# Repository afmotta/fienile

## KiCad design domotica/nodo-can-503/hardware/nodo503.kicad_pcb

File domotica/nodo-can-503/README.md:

# Nodo CAN 503 – ESP32-C6-WROOM-1 (rev C)

Nodo per la domotica CAN del fienile, da montare in scatola 503: un morsetto per 24 V e bus CAN, transceiver TJA1051T/3, 6 ingressi pulsante, porta Qwiic (I²C) e modulo **ESP32-C6-WROOM-1-N8** (LCSC C5366877) con Wi-Fi per ESPHome e aggiornamenti OTA. È pensato per il montaggio completo da JLCPCB, con tutti i componenti su un solo lato.

- **Dimensioni:** 56 × 41 mm (come la CANBed RP2040), 2 strati, spessore 1,6 mm, rame 1 oz
- **Fissaggio:** 4 fori M3 non metallizzati (Ø 3,2 mm) negli angoli, con il centro a 3,5 mm dai bordi: interasse **49 × 34 mm**. Entro 3,3 mm dal centro di ogni foro non passano piste né via, così la testa della vite (fino a Ø 6 mm) appoggia solo su piano di massa coperto da solder mask. Il foro in alto a sinistra è a circa 4 mm dall'antenna: lì usa una vite in nylon o un perno di plastica.
- **Progetto:** KiCad 7 (si apre anche in KiCad 8/9)
- **Simbolo e footprint del modulo:** dalla libreria ufficiale [espressif/kicad-libraries](https://github.com/espressif/kicad-libraries), licenza CC-BY-SA 4.0. Il footprint comprende anche l'area dell'antenna senza rame.

## Contenuto della cartella

Questa cartella (`domotica/nodo-can-503/` nel repository `afmotta/fienile`) contiene tutto il progetto della scheda; i percorsi sono relativi a qui.

| Percorso | Cosa contiene |
|---|---|
| `hardware/nodo503.kicad_pro / .kicad_sch / .kicad_pcb` | Progetto KiCad 7 completo (si apre con KiCad 7, 8 o 9) |
| `hardware/nodo503.kicad_sym`, `hardware/nodo503.pretty/` | Simbolo e footprint del modulo ESP32-C6-WROOM-1 (libreria di progetto) |
| `hardware/out/gerber_JLCPCB.zip` | Gerber + foratura, da caricare così com'è su JLCPCB |
| `hardware/out/BOM.csv`, `CPL_JLCPCB.csv` | Distinta e piazzamento per il montaggio completo (SMD + THT) |
| `hardware/out/BOM_SMD.csv`, `CPL_SMD.csv` | Distinta e piazzamento solo SMD |
| `hardware/out/nodo503_schema.pdf`, `anteprima_lato_*.png` | Schema elettrico e anteprime rame + serigrafia |
| `hardware/jlc_library.json` | Libreria JLCPCB (Basic / Preferred / Extended) di ogni codice LCSC |
| `hardware/*.py`, `hardware/*.sh` | Script che generano schema, PCB, sbroglio e file di produzione (vedi [docs/pipeline.md](docs/pipeline.md)) |
| `docs/decisioni.md` | Storia del progetto e motivazioni delle scelte |
| `docs/pipeline.md` | Come rigenerare tutto, struttura degli script, problemi noti |
| `CLAUDE.md` | Contesto per le sessioni di Claude Code che lavoreranno sul progetto |
| `tools/setup.sh` | Installa KiCad 7, Freerouting 1.9.0 e le dipendenze Python |

Per rigenerare i file di produzione dopo una modifica: `sudo tools/setup.sh` (una volta), poi `hardware/route.sh` se cambiano piazzamento o collegamenti, `hardware/build_pcb.sh` se basta lo sbroglio salvato, e infine `hardware/export.sh`.

## Circuito

- **Ingresso 24 V:** PTC da 0,5 A (F1), diodo SS34 contro l'inversione di polarità (D1), TVS SMBJ26CA (D2), elettrolitico da 22 µF e MLCC da 10 µF 50 V in ingresso.
- **5 V:** MORNSUN K7805-500R3 (U1), switching con pin compatibili 7805. Alimenta il TJA1051.
- **3,3 V:** LDO AP2112K-3.3 (U4, 600 mA). Due diodi B5819W (D3, D5) in "OR" lo alimentano dai 5 V del K7805 oppure dai 5 V del pettine di programmazione: il modulo si programma anche senza i 24 V, e la tensione dell'USB non risale verso il K7805.
- **CAN:** TJA1051T/3 con VIO a 3,3 V (nessun partitore sulle linee logiche), pin S a GND, protezione ESD NUP2105L sulle linee del bus. **Nessuna terminazione da 120 Ω** a bordo: il bus va terminato agli estremi della linea.
- **Microcontrollore:** modulo ESP32-C6-WROOM-1-N8 (flash 8 MB, antenna su PCB), con l'antenna a filo del bordo superiore della scheda. Rete RC su EN (10 kΩ + 1 µF) e pull-up da 10 kΩ su GPIO8, come raccomanda Espressif.
- **Ingressi pulsante:** per ciascuno pull-up da 10 kΩ a 3,3 V, resistenza in serie da 1 kΩ e condensatore da 100 nF verso GND (τ ≈ 100 µs). Il pulsante chiude verso GND (logica attiva bassa). Componenti 0402, sotto il bordo inferiore del modulo.

## Pinout

| Funzione | GPIO | Pin modulo WROOM |
|---|---|---|
| CAN TXD | GPIO23 | 21 |
| CAN RXD | GPIO22 | 20 |
| Pulsante 1 | GPIO7 | 7 |
| Pulsante 2 | GPIO0 | 8 |
| Pulsante 3 | GPIO1 | 9 |
| Pulsante 4 | GPIO20 | 18 |
| Pulsante 5 | GPIO19 | 17 |
| Pulsante 6 | GPIO18 | 16 |
| Qwiic SDA | GPIO3 | 26 |
| Qwiic SCL | GPIO2 | 27 |
| USB D− / D+ (programmazione) | GPIO12 / GPIO13 | 13 / 14 |
| BOOT (pin 5 di J4) | GPIO9 | 15 |
| Pull-up di boot | GPIO8 | 10 |
| Liberi | GPIO4, 5, 6, 10, 11, 15, 16, 17, 21 | – |

Rispetto alla versione 48 × 44 mm i GPIO di pulsanti, Qwiic e CAN sono cambiati: i pulsanti 1–3 usano i pin del lato sinistro del modulo, i pulsanti 4–6 quelli del lato destro, così le piste non si incrociano. GPIO4, GPIO5, GPIO8, GPIO9 e GPIO15 sono pin di strapping: se in futuro ne usi uno, tieni conto del livello che deve avere all'avvio.

## Connettori

- **J1 BUS:** morsetto passo 3,5 mm sul bordo destro, fili che entrano da destra. Dall'alto in basso: 24V – GND – CAN-H – CAN-L.
- **J2 PULSANTI:** morsetto estraibile verticale a 7 poli, passo 3,5 mm, sul bordo inferiore. Sulla scheda c'è la presa (Kefa KF2EDGV-3.5-7P); i fili vanno nella spina a vite (KF2EDGK-3.5-7P), che si innesta dall'alto, quindi i fili escono perpendicolari alla scheda. Cabli la spina sui pulsanti e poi la innesti: per staccare la scheda basta sfilarla. Pin da sinistra: pulsanti 1, 2, 3, 4, 5, 6, GND.
- **Comune dei pulsanti:** c'è un solo morsetto GND. Fai i ponticelli del comune tra i pulsanti sulla placca e porta un solo filo alla spina. Se preferisci due fili fino alla spina, il morsetto da 1,5 mm² ne accetta due da 0,5 mm², meglio con un puntale doppio.
- **Filo per i pulsanti:** la corrente è di circa 0,3 mA, quindi la sezione conta solo per la meccanica. Consigliata cordina da **0,5 mm²** (la spina accetta da 0,2 a 1,5 mm²). Se nella scatola o nei tubi passano anche conduttori a 230 V, il filo deve avere un isolamento adatto a quella tensione (ad esempio FS17 o H05V-K da 0,5 mm²).
- **J3 Qwiic:** JST SH a 4 pin, passo 1 mm, sul bordo superiore a destra con l'imbocco verso l'alto. GND, 3,3 V, SDA, SCL. **Nessun pull-up I²C sulla scheda:** li forniscono il QwiicBus e le schede dei sensori.
- **J4 PROG:** pettine verticale 1×6 a passo 2,54 mm sul lato sinistro, da non montare. Pin: 5V, D−, D+, GND, BOOT, GND. I pin 1–4 vanno al cavo USB (USB nativo del C6). Un ponticello sui pin 5–6 porta GPIO9 a massa e fa partire il modulo in modalità download.

Nessuna terminazione da 120 Ω sulla scheda: il bus va terminato agli estremi della linea.

## Prima programmazione

1. Collega un cavo USB al pettine J4: rosso al 5V, bianco a D−, verde a D+, nero a GND. Puoi usare un connettore a pettine o delle punte a molla (pogo pin).
2. Con il flash vuoto il modulo di solito entra da solo in modalità download. Se non succede, o se un firmware difettoso ha bloccato l'USB:
   - metti un ponticello sui pin 5–6 di J4 (BOOT–GND);
   - collega l'USB, oppure accendi la scheda;
   - programma, poi **togli il ponticello**. Se lo lasci, il modulo resta in modalità download a ogni riavvio e il firmware non parte.
3. Programma con ESPHome (o esptool) via USB. Dal flash successivo puoi usare l'OTA via Wi-Fi.

## Da verificare prima dell'ordine

1. **Codici LCSC e magazzino.** Tutti i componenti montati hanno un codice LCSC. Al caricamento della BOM controlla la disponibilità, soprattutto di J3 (vedi sotto).
2. **Rotazioni nel file CPL.** Controllale nell'anteprima di assemblaggio JLCPCB, soprattutto per il modulo U3 (l'antenna deve stare a filo del bordo superiore, sopra l'area senza rame), U2, U4 (ruotato di 180°), J3 (ruotato di 180°, imbocco verso l'alto), J1 (ruotato di 90°), J2 (il lato con l'incastro della spina deve coincidere con quello del footprint), i diodi e C1.
3. **Via nel pad di massa del modulo.** Il pad di massa sotto il WROOM è una griglia 3×3 con 5 via verso la massa sul retro. Su JLCPCB conviene chiedere che le via siano tappate ("via-in-pad" o "epoxy filled"), così lo stagno non cola nei fori. Se non lo fai, di solito funziona comunque.
4. **Piste sotto il modulo.** La pista di BOOT passa sullo strato superiore sotto il bordo inferiore del modulo, lontano dall'antenna; altre piste passano sul retro sotto il modulo. È ammesso, ma se in KiCad vuoi un piano di massa più pulito sotto il modulo puoi spostarle sul retro.

## Montaggio

- **Montaggio completo:** carica `BOM.csv` e `CPL_JLCPCB.csv`. JLCPCB monta anche i THT (K7805-500R3, J1 e la presa J2) a onda o a mano. Non resta nulla da saldare, J4 resta senza componente. La spina KF2EDGK-3.5-7P si ordina a parte.
- **Solo SMD:** carica `BOM_SMD.csv` e `CPL_SMD.csv`. Il K7805, J1 e la presa J2 restano da saldare a mano.

## Esempio ESPHome (indicativo)

```yaml
esp32:
  board: esp32-c6-devkitc-1
  variant: esp32c6
  framework:
    type: esp-idf

canbus:
  - platform: esp32_can
    tx_pin: GPIO23
    rx_pin: GPIO22
    can_id: 0x101
    bit_rate: 125kbps

i2c:
  sda: GPIO3
  scl: GPIO2
  scan: true

binary_sensor:
  - platform: gpio
    name: "Pulsante 1"
    pin:
      number: GPIO7
      inverted: true
      mode: { input: true, pullup: false }   # pull-up esterno da 10k
    filters:
      - delayed_on_off: 20ms
  # Pulsanti 2–6: GPIO0, GPIO1, GPIO20, GPIO19, GPIO18
```

## BOM e librerie JLCPCB (aggiornata il 2026-10-14)

Tutti i componenti hanno un codice LCSC e sono pensati per il montaggio completo da JLCPCB, compresi i THT (J1, J2 e K7805 U1, saldati da JLCPCB a onda o a mano). La colonna **Libreria JLCPCB** della BOM indica Basic / Preferred / Extended; l'elenco usato è in `hardware/jlc_library.json`.

- **Non montati:** solo **J4** (pettine di programmazione, DNP). Per programmare si usano pin a pressione o un pettine inserito al momento.
- **C2** è passato da 2,2 µF a **10 µF 50 V 1206** (C13585, Basic): più capacità in ingresso al K7805 e un componente Extended in meno.
- **C1:** Panasonic EEE-FK1H220P (C128458), 6,3 × 5,8 mm. È compatibile con il footprint 6,3 × 5,4 mm.
- **J1:** DORABO DB125-3.5-4P-GN-S (C2757925, Extended, saldatura a onda, disponibile anche in PCBA Economic), passo 3,5 mm, ingresso fili laterale, vite M2, filo fino a 1 mm². Il passo coincide con il footprint Phoenix PT 1,5/4-3,5-H. Prima dell'ordine verifica nell'anteprima JLCPCB che il corpo e il lato d'ingresso dei fili coincidano.
- **J2:** presa Kefa KF2EDGV-3.5-7P (C441326, Extended, saldatura a onda, PCBA Economic e Standard), footprint Phoenix MCV 1,5/7-G-3,5 verticale. A magazzino LCSC ce n'erano 485 il 2026-10-14.
- **Spina per J2 da ordinare a parte:** Kefa KF2EDGK-3.5-7P (LCSC C440852, circa 0,52 $ da 10 pezzi). Non è nella BOM di montaggio perché non si salda: si aggiunge all'ordine LCSC. Il 2026-10-14 ce n'erano solo 234: comprale con il primo ordine, con qualcuna di scorta. Se finissero, la soluzione di riserva sono due 4 poli (KF2EDGV/KF2EDGK-3.5-4P, C441323/C440849, molto disponibili), ma servirebbe rifare il PCB. 
- **CPL:** per i THT la posizione è il centro dei pin (non il pin 1). Controlla nell'anteprima di assemblaggio le rotazioni dei morsetti e del K7805.
- **J3 (C160404) ha pochissimi pezzi a magazzino.** Alternative compatibili Qwiic (Extended, da confrontare con il footprint): ZX-SH1.0-4PWT C7430446, HC-1.0-4PWT C2845363, BX-SH1.0-4PWT C18077910.
- Le pagine JLCPCB dei componenti Preferred mostrano solo "Extended": al caricamento della BOM verifica che abbiano il badge "Preferred".

## Storia e decisioni

La storia del progetto (rev A con XIAO, rev B con MINI-1, revisione di un esperto, passaggio a 56 × 41 mm, scelta dei connettori) e il motivo di ogni scelta sono in [docs/decisioni.md](docs/decisioni.md).

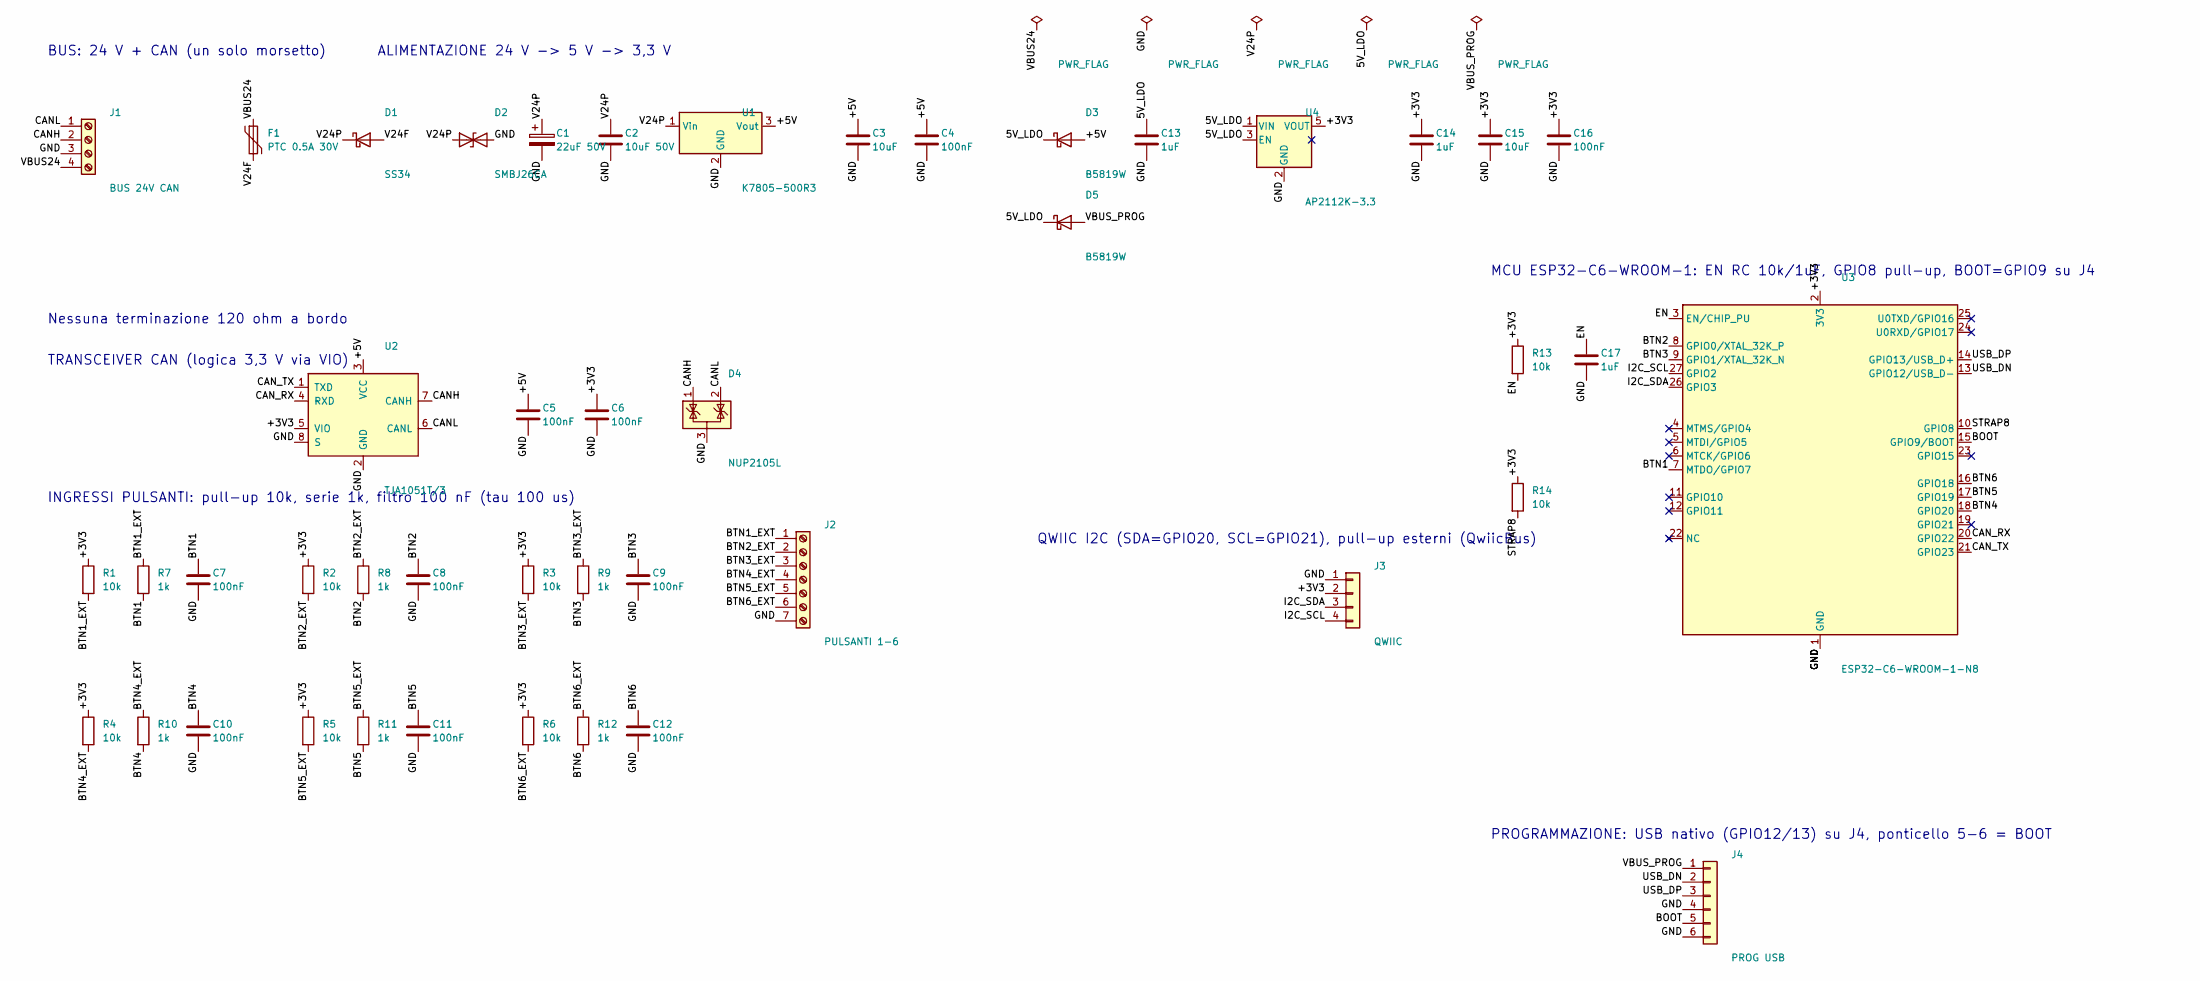
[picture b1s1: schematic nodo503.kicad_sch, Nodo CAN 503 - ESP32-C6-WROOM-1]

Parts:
C1: 22uF 50V; CP_Elec_6.3x5.4; MPN Panasonic EEE-FK1H220P, elettrolitico S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; LCSC C128458
C2: 10uF 50V; C_1206_3216Metric; MPN MLCC 10 uF 50 V X5R 1206 (Samsung CL31A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; LCSC C13585
C3: 10uF; C_0805_2012Metric; MPN MLCC 10 uF 25 V 0805; LCSC C15850
C4, C5, C6, C16: 100nF; C_0603_1608Metric; MPN MLCC 100 nF 50 V 0603; LCSC C14663
C7, C8, C9, C10, C11, C12: 100nF; C_0402_1005Metric; MPN MLCC 100 nF 0402; LCSC C1525
C13, C14: 1uF; C_0603_1608Metric; MPN MLCC 1 uF 50 V X5R 0603 (Samsung CL10A1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; LCSC C15849
C15: 10uF; C_0603_1608Metric; MPN MLCC 10 uF 10 V X5R 0603 (Samsung CL10A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; LCSC C19702
C17: 1uF; C_0402_1005Metric; MPN MLCC 1 uF 25 V X5R 0402 (Samsung CL05A1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; LCSC C52923
D1: SS34; D_SMA; MPN SS34 (40 V 3 A) - protezione inversione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; LCSC C8678
D2: SMBJ26CA; D_SMB; MPN SMBJ26CA TVS bidirezionale 26 V, SMB (h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; LCSC C19077581
D3: B5819W; D_SOD-123; MPN B5819W - OR alimentazione LDO (da 5 V b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; LCSC C8598
D4: NUP2105L; SOT-23; MPN onsemi NUP2105LT1G - ESD bus CAN 24 V; LCSC C14486
D5: B5819W; D_SOD-123; MPN B5819W - OR alimentazione LDO (da USB d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; LCSC C8598
F1: PTC 0.5A 30V; Fuse_1812_4532Metric; MPN PTC 1812 RUILON SMD1812P050TF/30 (0,5 A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; LCSC C12559
J1: BUS 24V CAN; TerminalBlock_Phoenix_PT-1,5-4-3.5-H_1x04_P3.50mm_Horizontal; MPN Morsetto a vite 4 poli passo 3,5 mm, DO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; LCSC C2757925
J2: PULSANTI 1-6; PhoenixContact_MCV_1,5_7-G-3.5_1x07_P3.50mm_Vertical; MPN Presa per morsetto estraibile verticale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; LCSC C441326
J3: QWIIC; JST_SH_SM04B-SRSS-TB_1x04-1MP_P1.00mm_Horizontal; MPN JST SM04B-SRSS-TB(LF)(SN) (Qwiic, SH 1 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; LCSC C160404
J4: PROG USB; PinHeader_1x06_P2.54mm_Vertical; MPN Pettine 1x6 2,54 mm (non montato): 5V, 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
R1, R2, R3, R4, R5, R6, R13: 10k; R_0402_1005Metric; MPN 10 kOhm 1% 0402; LCSC C25744
R7, R8, R9, R10, R11, R12: 1k; R_0402_1005Metric; MPN 1 kOhm 1% 0402; LCSC C11702
R14: 10k; R_0402_1005Metric; MPN 10 kOhm 1% 0402 (GPIO8 alto al boot); LCSC C25744
U1: K7805-500R3; Converter_DCDC_TRACO_TSR-1_THT; MPN MORNSUN K7805-500R3 (6,5-36 V -> 5 V 0,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; LCSC C86735
U2: TJA1051T/3; SOIC-8_3.9x4.9mm_P1.27mm; MPN NXP TJA1051T/3/1J; LCSC C38695
U3: ESP32-C6-WROOM-1-N8; ESP32-C6-WROOM-1; MPN Espressif ESP32-C6-WROOM-1-N8; LCSC C5366877
U4: AP2112K-3.3; SOT-23-5; MPN Diodes AP2112K-3.3TRG1 (LDO 600 mA); LCSC C51118

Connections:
5V_LDO: C13.1, D3.1 (K), D5.1 (K), U4.1 (VIN), U4.3 (EN)
+3V3: C6.1, C14.1, C15.1, C16.1, J3.2, R1.1, R2.1, R3.1, R4.1, R5.1, R6.1, R13.1, R14.1, U2.5 (VIO), U3.2 (3V3), U4.5 (VOUT)
+5V: C3.1, C4.1, C5.1, D3.2 (A), U1.3 (Vout), U2.3 (VCC)
BOOT: J4.5, U3.15 (GPIO9/BOOT)
BTN1: C7.1, R7.2, U3.7 (MTDO/GPIO7)
BTN1_EXT: J2.1, R1.2, R7.1
BTN2: C8.1, R8.2, U3.8 (GPIO0/XTAL_32K_P)
BTN2_EXT: J2.2, R2.2, R8.1
BTN3: C9.1, R9.2, U3.9 (GPIO1/XTAL_32K_N)
BTN3_EXT: J2.3, R3.2, R9.1
BTN4: C10.1, R10.2, U3.18 (GPIO20)
BTN4_EXT: J2.4, R4.2, R10.1
BTN5: C11.1, R11.2, U3.17 (GPIO19)
BTN5_EXT: J2.5, R5.2, R11.1
BTN6: C12.1, R12.2, U3.16 (GPIO18)
BTN6_EXT: J2.6, R6.2, R12.1
CANH: D4.1 (K), J1.2, U2.7 (CANH)
CANL: D4.2 (K), J1.1, U2.6 (CANL)
CAN_RX: U2.4 (RXD), U3.20 (GPIO22)
CAN_TX: U2.1 (TXD), U3.21 (GPIO23)
EN: C17.1, R13.2, U3.3 (EN/CHIP_PU)
GND: C1.2, C2.2, C3.2, C4.2, C5.2, C6.2, C7.2, C8.2, C9.2, C10.2, C11.2, C12.2, C13.2, C14.2, C15.2, C16.2, C17.2, D2.2 (A2), D4.3 (A), J1.3, J2.7, J3.1, J4.4, J4.6, U1.2 (GND), U2.2 (GND), U2.8 (S), U3.1 (GND), U3.28 (GND), U3.29 (GND), U4.2 (GND)
I2C_SCL: J3.4, U3.27 (GPIO2)
I2C_SDA: J3.3, U3.26 (GPIO3)
STRAP8: R14.2, U3.10 (GPIO8)
USB_DN: J4.2, U3.13 (GPIO12/USB_D-)
USB_DP: J4.3, U3.14 (GPIO13/USB_D+)
V24F: D1.2 (A), F1.2
V24P: C1.1, C2.1, D1.1 (K), D2.1 (A1), U1.1 (Vin)
VBUS24: F1.1, J1.4
VBUS_PROG: D5.2 (A), J4.1

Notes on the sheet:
BUS: 24 V + CAN (un solo morsetto)
ALIMENTAZIONE 24 V -> 5 V -> 3,3 V
Nessuna terminazione 120 ohm a bordo
TRANSCEIVER CAN (logica 3,3 V via VIO)
MCU ESP32-C6-WROOM-1: EN RC 10k/1uF, GPIO8 pull-up, BOOT=GPIO9 su J4
PROGRAMMAZIONE: USB nativo (GPIO12/13) su J4, ponticello 5-6 = BOOT
QWIIC I2C (SDA=GPIO20, SCL=GPIO21), pull-up esterni (QwiicBus)
INGRESSI PULSANTI: pull-up 10k, serie 1k, filtro 100 nF (tau 100 us)

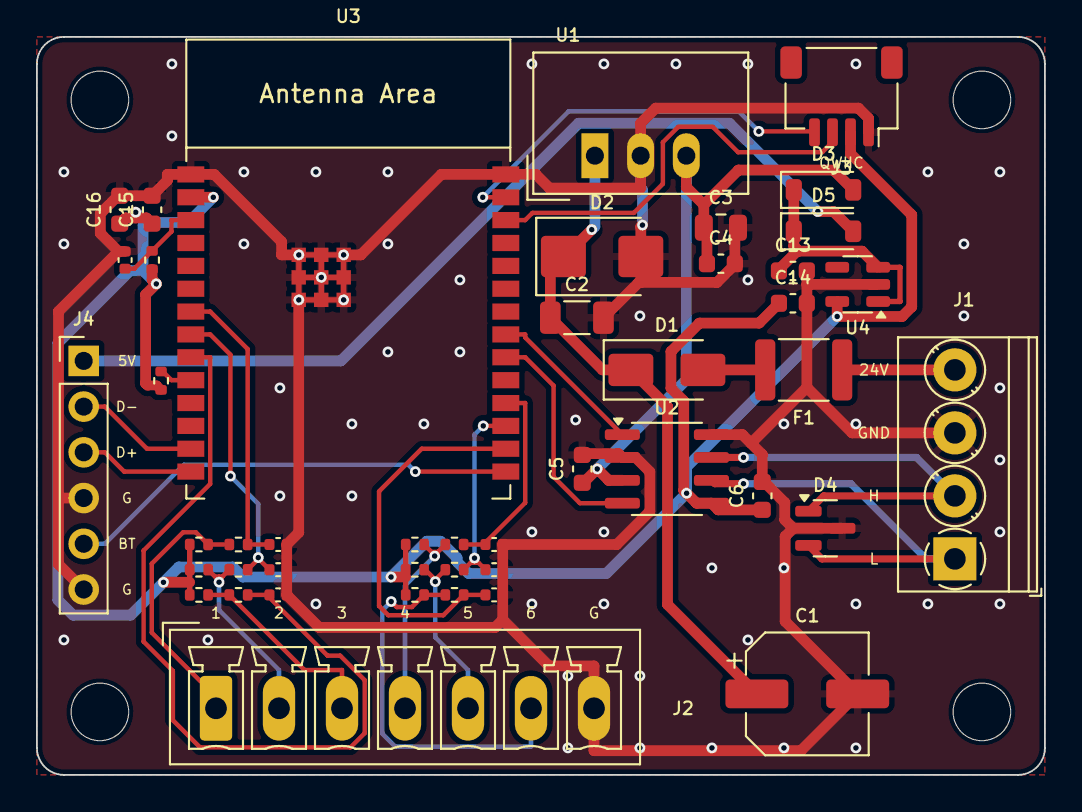
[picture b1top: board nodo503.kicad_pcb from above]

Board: 2 copper layers, 56.0 x 41.0 mm, 49 parts (0 on the bottom side), 31 nets.

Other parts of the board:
H1, H2, H3, H4: M3; MountingHole_3.2mm_M3

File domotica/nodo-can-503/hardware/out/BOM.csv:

Comment,Designator,Footprint,Quantita,Descrizione / MPN,LCSC,Libreria JLCPCB
22uF 50V,C1,CP_Elec_6.3x5.4,1,"Panasonic EEE-FK1H220P, elettrolitico SMD 22 uF 50 V, D6.3x5.8 mm, 105 C",C128458,Extended
10uF 50V,C2,C_1206_3216Metric,1,MLCC 10 uF 50 V X5R 1206 (Samsung CL31A106KBHNNNE),C13585,Basic
10uF,C3,C_0805_2012Metric,1,MLCC 10 uF 25 V 0805,C15850,Basic
100nF,"C4,C5,C6,C16",C_0603_1608Metric,4,MLCC 100 nF 50 V 0603,C14663,Basic
100nF,"C7,C8,C9,C10,C11,C12",C_0402_1005Metric,6,MLCC 100 nF 0402,C1525,Basic
1uF,"C13,C14",C_0603_1608Metric,2,MLCC 1 uF 50 V X5R 0603 (Samsung CL10A105KB8NNNC),C15849,Basic
10uF,C15,C_0603_1608Metric,1,"MLCC 10 uF 10 V X5R 0603 (Samsung CL10A106KP8NNNC), vicino al modulo",C19702,Basic
1uF,C17,C_0402_1005Metric,1,MLCC 1 uF 25 V X5R 0402 (Samsung CL05A105KA5NQNC) - RC su EN,C52923,Basic
SS34,D1,D_SMA,1,SS34 (40 V 3 A) - protezione inversione polarita',C8678,Basic
SMBJ26CA,D2,D_SMB,1,"SMBJ26CA TVS bidirezionale 26 V, SMB (hongjiacheng)",C19077581,Preferred
B5819W,D3,D_SOD-123,1,B5819W - OR alimentazione LDO (da 5 V bus),C8598,Basic
NUP2105L,D4,SOT-23,1,onsemi NUP2105LT1G - ESD bus CAN 24 V,C14486,Extended
B5819W,D5,D_SOD-123,1,B5819W - OR alimentazione LDO (da USB di programmazione),C8598,Basic
PTC 0.5A 30V,F1,Fuse_1812_4532Metric,1,"PTC 1812 RUILON SMD1812P050TF/30 (0,5 A hold, 30 V)",C12559,Extended
BUS 24V CAN,J1,"TerminalBlock_Phoenix_PT-1,5-4-3.5-H_1x04_P3.50mm_Horizontal",1,"Morsetto a vite 4 poli passo 3,5 mm, DORABO DB125-3.5-4P-GN-S (THT)",C2757925,Extended - THT (saldatura a onda/manuale JLCPCB)
PULSANTI 1-6,J2,"PhoenixContact_MCV_1,5_7-G-3.5_1x07_P3.50mm_Vertical",1,"Presa per morsetto estraibile verticale 7 poli passo 3,5 mm, Kefa KF2EDGV-3.5-7P (THT); spina KF2EDGK-3.5-7P C440852 da ordinare a parte",C441326,Extended - THT (saldatura a onda/manuale JLCPCB)
QWIIC,J3,JST_SH_SM04B-SRSS-TB_1x04-1MP_P1.00mm_Horizontal,1,"JST SM04B-SRSS-TB(LF)(SN) (Qwiic, SH 1 mm, orizzontale)",C160404,Extended
PROG USB,J4,PinHeader_1x06_P2.54mm_Vertical,1,"Pettine 1x6 2,54 mm (non montato): 5V, D-, D+, GND, BOOT, GND - ponticello 5-6 = download",,non montato (DNP)
10k,"R1,R2,R3,R4,R5,R6,R13",R_0402_1005Metric,7,10 kOhm 1% 0402,C25744,Basic
1k,"R7,R8,R9,R10,R11,R12",R_0402_1005Metric,6,1 kOhm 1% 0402,C11702,Basic
10k,R14,R_0402_1005Metric,1,10 kOhm 1% 0402 (GPIO8 alto al boot),C25744,Basic
K7805-500R3,U1,Converter_DCDC_TRACO_TSR-1_THT,1,"MORNSUN K7805-500R3 (6,5-36 V -> 5 V 0,5 A, SIP-3, pin 78xx)",C86735,Extended - THT (saldatura a onda/manuale JLCPCB)
TJA1051T/3,U2,SOIC-8_3.9x4.9mm_P1.27mm,1,NXP TJA1051T/3/1J,C38695,Extended
ESP32-C6-WROOM-1-N8,U3,ESP32-C6-WROOM-1,1,Espressif ESP32-C6-WROOM-1-N8,C5366877,Extended
AP2112K-3.3,U4,SOT-23-5,1,Diodes AP2112K-3.3TRG1 (LDO 600 mA),C51118,Extended

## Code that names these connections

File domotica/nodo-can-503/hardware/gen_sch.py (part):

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    ("1", "GND", "power_in", 0, -33.02, 90), ("28", "GND", "passive", 0, -33.02, 90), ("29", "GND", "passive", 0, -33.02, 90),
    ("2", "3V3", "power_in", 0, 33.02, 270),
    ("3", "EN/CHIP_PU", "input", -27.94, 27.94, 0),
    ("8", "GPIO0/XTAL_32K_P", "bidirectional", -27.94, 22.86, 0), ("9", "GPIO1/XTAL_32K_N", "bidirectional", -27.94, 20.32, 0),
    ("27", "GPIO2", "bidirectional", -27.94, 17.78, 0), ("26", "GPIO3", "bidirectional", -27.94, 15.24, 0),
    ("4", "MTMS/GPIO4", "bidirectional", -27.94, 7.62, 0), ("5", "MTDI/GPIO5", "bidirectional", -27.94, 5.08, 0),
    ("6", "MTCK/GPIO6", "bidirectional", -27.94, 2.54, 0), ("7", "MTDO/GPIO7", "bidirectional", -27.94, 0, 0),
    ("11", "GPIO10", "bidirectional", -27.94, -5.08, 0), ("12", "GPIO11", "bidirectional", -27.94, -7.62, 0),
    ("22", "NC", "no_connect", -27.94, -12.7, 0),
    ("25", "U0TXD/GPIO16", "bidirectional", 27.94, 27.94, 180), ("24", "U0RXD/GPIO17", "bidirectional", 27.94, 25.4, 180),
    ("14", "GPIO13/USB_D+", "bidirectional", 27.94, 20.32, 180), ("13", "GPIO12/USB_D-", "bidirectional", 27.94, 17.78, 180),
    ("10", "GPIO8", "bidirectional", 27.94, 7.62, 180), ("15", "GPIO9/BOOT", "bidirectional", 27.94, 5.08, 180),
    ("23", "GPIO15", "bidirectional", 27.94, 2.54, 180), ("16", "GPIO18", "bidirectional", 27.94, -2.54, 180),
    ("17", "GPIO19", "bidirectional", 27.94, -5.08, 180), ("18", "GPIO20", "bidirectional", 27.94, -7.62, 180),
    ("19", "GPIO21", "bidirectional", 27.94, -10.16, 180), ("20", "GPIO22", "bidirectional", 27.94, -12.7, 180),
    ("21", "GPIO23", "bidirectional", 27.94, -15.24, 180),
]

def mod_sym(name):
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
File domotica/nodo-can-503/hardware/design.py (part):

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       # buttons 1-3 on the left pins, 4-6 on the right pins (both towards J2)
       "7": "BTN1", "8": "BTN2", "9": "BTN3", "18": "BTN4", "17": "BTN5", "16": "BTN6",
       "13": "USB_DN", "14": "USB_DP", "10": "STRAP8", "15": "BOOT",
       "26": "I2C_SDA", "27": "I2C_SCL", "21": "CAN_TX", "20": "CAN_RX"}   # TX above RX, like TJA1051 pins 1 and 4
for n in ["4", "5", "6", "11", "12", "19", "22", "23", "24", "25"]:
    mod[n] = None
MODX, MODY = 17.3, 15.9      # module origin; antenna keep-out flush with the top edge
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add("C17", "Device:C", "1uF", C0402, {"1": "EN", "2": "GND"}, (302.26, 86.36), (4.9, 12.4, 90),
    mpn="MLCC 1 uF 25 V X5R 0402 (Samsung CL05A105KA5NQNC) - RC su EN", lcsc="C52923")
add("R14", "Device:R", "10k", R0402, {"1": "+3V3", "2": "STRAP8"}, (289.56, 111.76), (6.9, 19.1, 90),
    mpn="10 kOhm 1% 0402 (GPIO8 alto al boot)", lcsc="C25744")
add("J4", "Connector_Generic:Conn_01x06", "PROG USB", "Connector_PinHeader_2.54mm:PinHeader_1x06_P2.54mm_Vertical",
    {"1": "VBUS_PROG", "2": "USB_DN", "3": "USB_DP", "4": "GND", "5": "BOOT", "6": "GND"}, (325.12, 185.42), (2.6, 18.0, 0),
    mpn="Pettine 1x6 2,54 mm (non montato): 5V, D-, D+, GND, BOOT, GND - ponticello 5-6 = download")
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    (157.48, 127.0), (9.95, 37.3, 0),
    mpn="Presa per morsetto estraibile verticale 7 poli passo 3,5 mm, Kefa KF2EDGV-3.5-7P (THT); spina KF2EDGK-3.5-7P C440852 da ordinare a parte", lcsc="C441326")

# --- Qwiic / I2C (SDA = GPIO20, SCL = GPIO21) ---------------------------
add("J3", "Connector_Generic:Conn_01x04", "QWIIC", "Connector_JST:JST_SH_SM04B-SRSS-TB_1x04-1MP_P1.00mm_Horizontal",
    {"1": "GND", "2": "+3V3", "3": "I2C_SDA", "4": "I2C_SCL"}, (259.08, 129.54), (44.7, 3.3, 180),
    mpn="JST SM04B-SRSS-TB(LF)(SN) (Qwiic, SH 1 mm, orizzontale)", lcsc="C160404")
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    ("ALIMENTAZIONE 24 V -> 5 V -> 3,3 V", (78.74, 30.48)),
    ("Nessuna terminazione 120 ohm a bordo", (17.78, 80.01)),
    ("TRANSCEIVER CAN (logica 3,3 V via VIO)", (17.78, 87.63)),
    ("MCU ESP32-C6-WROOM-1: EN RC 10k/1uF, GPIO8 pull-up, BOOT=GPIO9 su J4", (284.48, 71.12)),
    ("PROGRAMMAZIONE: USB nativo (GPIO12/13) su J4, ponticello 5-6 = BOOT", (284.48, 175.26)),
    ("QWIIC I2C (SDA=GPIO20, SCL=GPIO21), pull-up esterni (QwiicBus)", (200.66, 120.65)),
    ("INGRESSI PULSANTI: pull-up 10k, serie 1k, filtro 100 nF (tau 100 us)", (17.78, 113.03)),
]

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
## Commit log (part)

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2026-02-26 Create CNAME
2026-02-26 add CONTEXT.md
2026-02-26 add primo piano variants and comparison page
    Add 4 first-floor window distribution variants (P1-A through P1-D)
    with different F2/F3 widths (160-200cm), per-room RAI calculations,
    and an interactive comparison page with selectors for all PT+P1
    combinations. Update index.html and CONTEXT.md accordingly.
2026-02-26 add room names to ground floor variants and comparison page
    Add Cucina/Soggiorno labels to SVG drawings, position tables,
    and per-room RAI breakdowns for all 5 ground floor variants.
    Update confronto.html to show room names for both floors.
2026-02-26 Switched the order of selectors in confronto
2026-02-27 add toggles to switch elements visibility - toggle to hide pillars - toggle to hide column
2026-02-27 fixed labels for boarders
2026-03-01 new variants and small alterations to existing one
2026-03-01 add rendering for kitchen forniture
2026-03-01 add gitingore
2026-03-01 add playground
2026-05-29 add src/ folder structure for future iterations
    src/piano-terra/ e src/primo-piano/ per l'iterazione corrente.
    src/archivio/ per i file di esplorazione fase decisionale.
